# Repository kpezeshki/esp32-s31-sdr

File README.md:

# ESP32-S31 SDR

A low-cost, receive-only, general-purpose SDR. It uses the ESP32-S31's raw I/Q streaming (community "esp-sdr" firmware: continuous 8-bit I/Q at 40 MS/s over gigabit Ethernet) behind a wideband mixer front end.

```
Board B (RF):   SMA ─ ESD ─ SP3T ─┬─ LB: PSA4-5043+ ─ LPF 1.75 GHz ─┐
                                  ├─ MB: PSA4-5043+ ─ BPF 1.75–2.15 ─┤─ SP3T ─ GVA-62+ ─ balun ─ RFFC5072 ─ 2.44 GHz SAW ─ pad ─ U.FL
                                  └─ HB: HPF ─ QPL9503 ─ HPF 3.1 GHz ┘
Board A (base): U.FL ─ ESP32-S31-WROOM-1U (raw I/Q) ─ RGMII ─ YT8531 ─ RJ45 (GbE);  USB-C;  2×10 header → Board B
```

Coverage:

| Band | Range | LO |
|---|---|---|
| LB | 50–1750 MHz | IF+RF |
| MB | 1750–2150 MHz | IF−RF |
| HB | 3.1–6 GHz | RF−IF |
| Native ESP32 (Board A alone) | 2.15–2.8 GHz | none |

The IF is 2440 MHz (61 × 40 MHz).

**Design report** (board renders, copper layers, simulated filters / noise figure / dynamic range, priced BOM, cost per board): [`docs/report/index.html`](docs/report/index.html). It can be served with GitHub Pages from `/docs`.

## Status (2026-11)
- Both boards are placed, routed and DRC-clean to the JLC basic 4-layer process (JLC04161H-3313 stack, 0.45/0.2 mm vias, 0.1/0.1 mm track/space).
- Gerbers, BOM and CPL are in `hw/board_{a,b}/fab/`.
- **Not yet fabricated or measured.** All performance numbers are simulated:

| | LB | MB | HB |
|---|---|---|---|
| Simulated NF | 1.4–2.1 dB | 2.5–3.1 dB | 2.2–3.0 dB |

- Instantaneous dynamic range is ≈44 dB in 40 MHz, limited by the 8-bit ADC.
- Cost: about $87 per system at qty 5, about $68 at qty 10. That is from LCSC prices; the PCB and shipping figures are estimates.
- Before ordering: run a JLC CPL/DFM preview, and check stock for the ESP32-S31 module and the RFFC5072.

## Repository layout
| Path | What |
|---|---|
| `SIGNAL_CHAIN_ANALYSIS.md`, `PART_SELECTION.md`, `RISK_RESEARCH.md`, `COST_PLAN.md` | Analysis: cascade and power levels, frequency plan and spurs, parts, risks, cost |
| `DECISIONS.md` | Decision log (D1–D22) |
| `SPLIT_ARCHITECTURE.md` | Why there are two boards (A: base / B: RF) and the header pinout |
| `analysis/` | Python models: cascade, frequency plan, lumped filter synthesis, cost |
| `em/` | Sonnet EM models of the 0402 filter layouts. EM-in-the-loop optimisation and Monte Carlo (`em/EM_REPORT.md`, `em/filters/FINAL_FILTERS.md`). `RLM_LICENSE` must be set to run Sonnet |
| `hw/design2.py` | Netlists for both boards (`build_a`, `build_b`) |
| `hw/placement_a.py`, `hw/placement_b.py` | Placement and scripted routes. Board A: module escapes, RGMII lanes, USB HS pair. Board B: RF chain exactly as EM-modelled |
| `hw/pcb2.py`, `hw/build_pcb.py`, `hw/footprints.py` | KiCad 10 board generation (pcbnew Python) and custom footprints (`hw/esp32_sdr.pretty`) |
| `hw/fr2.py`, `hw/run_freerouting.sh` | Freerouting flow: DSN export/SES import, incremental passes, scripted fixes. Freerouting runs network-isolated (see `claude_notes/FREEROUTING_AUDIT.md`) |
| `hw/stitch.py`, `hw/rm_dangling.py`, `hw/silk_clean.py`, `hw/render_routed.py` | Post-route: GND stitching, cleanup, silk, renders |
| `hw/board_a/`, `hw/board_b/` | KiCad boards (`*_routed.kicad_pcb`), DRC reports, `fab/` outputs, `shots/` images |
| `hw/report/` | Report generators (`cost_boards.py`, `rf_perf.py`, `build_report.py`) |
| `hw/LAYOUT_STATUS_SPLIT.md` | Layout status and open items |
| `hw/esp32_sdr*.kicad_pcb`, `hw/LAYOUT_STATUS.md`, `hw/router*.py`, `hw/fr_route.py`, `hw/bom.py`, `hw/fab/` | Superseded single-board design, kept for reference (replaced by the two-board split, D15) |

## Reproducing the boards
```
cd hw
python3 fr2.py A export && bash run_freerouting.sh fr-a board_a/esp32sdr_a.dsn board_a/esp32sdr_a.ses board_a/freerouting.log
python3 fr2.py A import && python3 stitch.py board_a/esp32sdr_a_routed.kicad_pcb 3.0 --edge-pitch 3.0 && python3 fr2.py A post
kicad-cli pcb drc --refill-zones --save-board -o board_a/drc_routed.rpt board_a/esp32sdr_a_routed.kicad_pcb
bash fab_export.sh a && python3 bom2.py A          # same for B (stitch pitch 2.5, edge 2.0)
```
Requirements:
- KiCad 10 with its Python bindings;
- Freerouting 2.1 and a Java 21 runtime;
- numpy, scipy and matplotlib;
- Sonnet 19 for the EM models.

Most of the design work was done with Claude (Anthropic) as an engineering agent. `claude_notes/` holds its working notes.

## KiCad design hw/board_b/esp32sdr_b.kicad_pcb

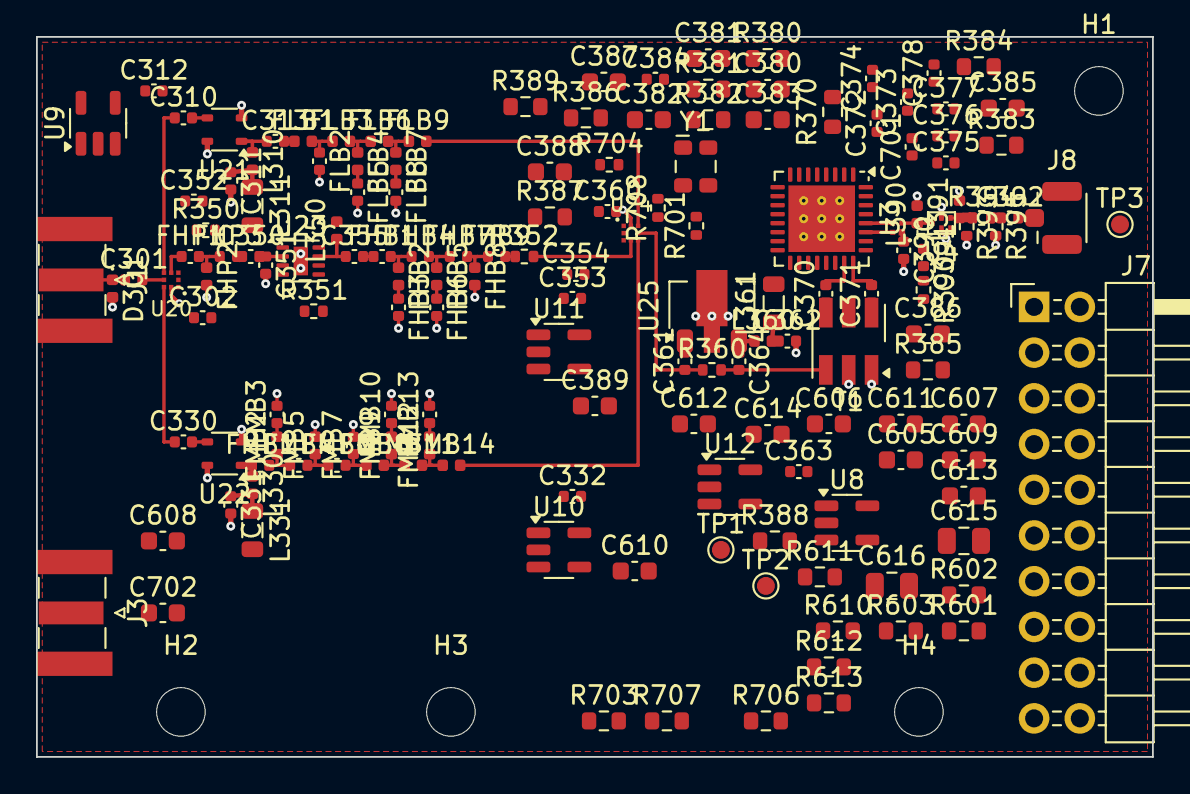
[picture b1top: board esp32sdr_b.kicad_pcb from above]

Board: 4 copper layers, 62.0 x 40.0 mm, 160 parts (0 on the bottom side), 98 nets.

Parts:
C301, C310, C313, C330, C361, C364, C370, C371: 1nF; C_0402_1005Metric
C302, C312, C332, C360, C363, C373, C375, C377, C384, C391, C701: 100nF; C_0402_1005Metric
C311, C331, C352, C353, C362, C390: 100pF; C_0402_1005Metric
C350: 10pF; C_0402_1005Metric
C351: 0.2pF; C_0402_1005Metric
C354: 1uF; C_0402_1005Metric
C355: 5.6pF; C_0402_1005Metric
C372, C374, C376, C378, C392: 33pF; C_0402_1005Metric
C380: 8.2pF; C_0603_1608Metric
C381: 180pF; C_0603_1608Metric
C382, C383: 330pF; C_0603_1608Metric
C385, C386, C387, C388, C389: 33pF; C_0603_1608Metric
C605, C607, C609, C611, C613: 1uF; C_0603_1608Metric
C606, C608, C610, C612, C614: 4.7uF; C_0603_1608Metric
C615: 22uF; C_0805_2012Metric
C616: 10uF; C_0805_2012Metric
C702: 100nF; C_0603_1608Metric
D301: KLXES15AAA1; D_0402_1005Metric
FHB1: 2.4pF; C_0402_1005Metric
FHB2: 2nH; L_0402_1005Metric
FHB3: 3pF; C_0402_1005Metric
FHB4, FHB9: 1pF; C_0402_1005Metric
FHB5: 1.5nH; L_0402_1005Metric
FHB6: 4.7pF; C_0402_1005Metric
FHB7: 0.8pF; C_0402_1005Metric
FHB8: 1.3nH; L_0402_1005Metric
FHP1: 2.4pF; C_0402_1005Metric
FHP2: 2nH; L_0402_1005Metric
FHP3: 1.8pF; C_0402_1005Metric
FLB1, FLB4: 3.9nH; L_0402_1005Metric
FLB2: 2.4pF; C_0402_1005Metric
FLB3: 4.7nH; L_0402_1005Metric
FLB5, FLB8: 1.1pF; C_0402_1005Metric
FLB6: 3.3nH; L_0402_1005Metric
FLB7: 2.7nH; L_0402_1005Metric
FLB9: 1nH; L_0402_1005Metric
FMB1, FMB7: 1.8pF; C_0402_1005Metric
FMB2: 10nH; L_0402_1005Metric
FMB3: 1.1pF; C_0402_1005Metric
FMB4, FMB10: 0.5pF; C_0402_1005Metric
FMB5: 5.1nH; L_0402_1005Metric
FMB6, FMB13: 0.8pF; C_0402_1005Metric
FMB8, FMB11: 3.9nH; L_0402_1005Metric
FMB9: 6.8nH; L_0402_1005Metric
FMB12, FMB14: 3.3nH; L_0402_1005Metric
H1, H2, H3, H4: M2.5; MountingHole_2.7mm_M2.5
J1: SMA_MIX; SMA_Samtec_SMA-J-P-X-ST-EM1_EdgeMount
J3: SMA_REF; SMA_Samtec_SMA-J-P-X-ST-EM1_EdgeMount
J7: To base board; PinHeader_2x10_P2.54mm_Horizontal
J8: U.FL IF out; U.FL_Hirose_U.FL-R-SMT-1_Vertical
L310, L330: 33nH; L_0402_1005Metric
L311, L331, L361: 1uH; L_0805_2012Metric
L350: 18nH; L_0402_1005Metric
L360: 22nH; L_0402_1005Metric
L390, L391: 3.9nH; L_0402_1005Metric
R350: 4.7k; R_0402_1005Metric
R351: 22k; R_0402_1005Metric
R352, R360, R390, R701, R704, R708: 0; R_0402_1005Metric
R370: 51k; R_0603_1608Metric
R380: 22k; R_0603_1608Metric
R381, R382: 470; R_0603_1608Metric
R383, R384, R385, R386, R387, R706: 1k; R_0603_1608Metric
R388, R389: 4.7k; R_0603_1608Metric
R393, R395: 300; R_0402_1005Metric
R394: 18; R_0402_1005Metric
R601, R602, R603, R610, R611, R612, R613: 100k; R_0603_1608Metric
R703: 49.9; R_0603_1608Metric
R707: 390; R_0603_1608Metric
T1: H3-TCM2-63WX+; Mini-Circuits_DB1627
T2: BD2425N50200AHF; Anaren_Xinger_0404_BD2425
TP1: RFFC_LD; TestPoint_Pad_D1.0mm
TP2: 3V0_RF; TestPoint_Pad_D1.0mm
TP3: VGB; TestPoint_Pad_D1.0mm
U3: RFFC5072; QFN-32-1EP_5x5mm_P0.5mm_EP3.7x3.7mm_ThermalVias
U4: SAFEA2G45MC0F0AR00; Filter_1411-5_1.4x1.1mm
U8: TPS7A2030PDBVR; SOT-23-5
U9, U10, U11, U12: TPS7A2045PDBVR; SOT-23-5
U20, U24: BGS13SN8; Infineon_PG-TSNP-8-1_1.1x1.1mm_P0.4mm
U21, U22: PSA4-5043+; SOT-343_SC-70-4
U23: QPL9503; DFN-8-1EP_2x2mm_P0.5mm_EP0.8x1.6mm
U25: GVA-62+; SOT-89-3
Y1: TG2520SMN 40MHz; Oscillator_SMD_SeikoEpson_TG2520SMN-xxx-xxxxxx-4Pin_2.5x2.0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

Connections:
3V0_RF: C372.1, C373.1, C374.1, C375.1, C376.1, C377.1, C606.1, C701.1, R388.2, R390.1, TP2.1, U3.5, U3.19, U3.22, U8.5, Y1.4
3V3: C302.1, C360.1, C616.1, J7.5, U20.1, U24.1
5V0: C605.1, C607.1, C609.1, C611.1, C613.1, C615.1, J7.1, J7.2, U8.1, U8.3, U9.1, U10.1, U11.1, U12.1, U12.3
ESPCLK_DIV: R706.2, R707.1, R708.1
ESP_REFCLK: J7.20, R706.1
EXTREF_AC: C702.2, R703.1, R704.1
EXT_LO_DEC: C378.1, U3.3
EXT_REF: C702.1, J3.1
FHB_M1: FHB2.2, FHB3.1
FHB_M3: FHB5.2, FHB6.1
FHB_N1: FHB1.2, FHB2.1, FHB4.1
FHB_N2: FHB4.2, FHB5.1, FHB7.1
FHB_N3: FHB7.2, FHB8.1, FHB9.1
FHP_N1: FHP1.2, FHP2.1, FHP3.1
FLB_M3: FLB4.2, FLB5.1
FLB_M5: FLB7.2, FLB8.1
FLB_N1: FLB1.2, FLB2.1, FLB3.1
FLB_N2: FLB3.2, FLB4.1, FLB6.1
FLB_N3: FLB6.2, FLB7.1, FLB9.1
FMB_M1: FMB2.2, FMB3.1
FMB_M7: FMB9.2, FMB10.1
FMB_M9: FMB12.2, FMB13.1
FMB_N1: FMB1.2, FMB2.1, FMB4.1
FMB_N2: FMB4.2, FMB5.1, FMB6.1
FMB_N3: FMB6.2, FMB7.1, FMB8.1
FMB_N4: FMB8.2, FMB9.1, FMB11.1
FMB_N5: FMB11.2, FMB12.1, FMB14.1
GB_CHK: C362.1, L360.2, L361.1
GB_I: C361.2, U25.1
GB_O: C364.1, L360.1, U25.3
GND: C302.2, C311.2, C312.2, C331.2, C332.2, C351.2, C352.2, C353.2, C354.2, C360.2, C362.2, C363.2, C372.2, C373.2, C374.2, C375.2, C376.2, C377.2, C378.2, C382.2, C383.2, C385.2, C386.2, C387.2, C388.2, C389.2, C390.2, C391.2, C605.2, C606.2, C607.2, C608.2, C609.2, C610.2, C611.2, C612.2, C613.2, C614.2, C615.2, C616.2, C701.2, D301.2, FHB3.2, FHB6.2, FHB8.2, FHP2.2, FLB2.2, FLB5.2, FLB8.2, FMB3.2, FMB5.2, FMB7.2, FMB10.2, FMB13.2, J1.2, J3.2, J7.3, J7.4, J7.6, J8.2, L390.2, L391.2, R351.2, R370.2, R389.2, R393.2, R395.2, R601.2, R602.2, R603.2, R610.2, R611.2, R612.2, R613.2, R703.2, R707.2, T1.1, T1.2, U3.12, U3.33, U4.2, U4.3, U4.5, U8.2, U9.2, U10.2, U11.2, U12.2, U20.8, U21.2, U21.4, U22.2, U22.4, U23.4, U23.6, U23.9, U24.8, U25.2, Y1.2
HB_F_IN: C355.2, FHB1.1
HB_HPF_O: FHB9.2, R352.1
HB_IN: FHP1.1, U20.4
HB_LNA_I: C350.2, C351.1, U23.2
HB_LNA_O: C355.1, L350.1, U23.7
HB_OUT: R352.2, U24.4
HB_PRE_O: C350.1, FHP3.2
HB_SD: R351.1, U23.5
HB_VBIAS: C352.1, R350.2, U23.1
IF_CT: C390.1, C391.1, R390.2, T2.1
IF_OP_N: T2.4, U3.27
IF_OP_P: T2.3, U3.28
IF_OUT: C392.2, J8.1
IF_SAW_O: L391.1, R393.1, R394.1, U4.4
IF_SE: L390.1, T2.2, U4.1
LB_CHK: C311.1, L310.2, L311.1
LB_F_IN: C313.2, FLB1.1
LB_IN: C310.1, U20.5
LB_LNA_I: C310.2, U21.3
LB_LNA_O: C313.1, L310.1, U21.1
LB_OUT: FLB9.2, U24.7
LDO_EN_HB: J7.19, R603.1, U11.3
LDO_EN_LB: J7.17, R601.1, U9.3
LDO_EN_MB: J7.18, R602.1, U10.3
LF1: C380.1, R380.1, U3.6
LF2: C380.2, C381.2, R381.1, U3.7
LF3: C383.1, R382.2, U3.8
LF_A: C381.1, R380.2
LF_B: C382.1, R381.2, R382.1
MB_CHK: C331.1, L330.2, L331.1
MB_IN: C330.1, U20.7
MB_LNA_I: C330.2, U22.3
MB_LNA_O: FMB1.1, L330.1, U22.1
MB_OUT: FMB14.2, U24.5
MIX_DRV: C364.2, R360.2, T1.3
MIX_IN_N: C371.1, T1.6
MIX_IN_P: C370.1, T1.4
MIX_IPN: C371.2, U3.24
MIX_IPP: C370.2, U3.23
PAD_O: C392.1, R394.2, R395.1
REFCLK_RF: C384.1, R701.2, R704.2, R708.2
REF_IN: C384.2, U3.10
RFFC_ENBL: J7.10, R386.1
RFFC_ENBL_I: C388.1, R386.2, U3.1
RFFC_ENX: J7.9, R385.1
RFFC_ENX_I: C387.1, R385.2, U3.30
RFFC_LD: J7.12, TP1.1, U3.26
RFFC_MODE: R389.1, U3.9
RFFC_RESETX: J7.11, R387.1
RFFC_RESETX_I: C389.1, R387.2, R388.1, U3.29
RFFC_REXT: R370.1, U3.4
RFFC_SCLK: J7.7, R383.1
RFFC_SCLK_I: C385.1, R383.2, U3.31
RFFC_SDATA: J7.8, R384.1
RFFC_SDATA_I: C386.1, R384.2, U3.32
RF_IN_SMA: C301.1, D301.1, J1.1
SW1_COM: C301.2, U20.6
SW2_COM: C361.1, R360.1, U24.6
SW2_V1: J7.15, R612.1, U24.3
SW2_V2: J7.16, R613.1, U24.2
SW_V1: J7.13, R610.1, U20.3
SW_V2: J7.14, R611.1, U20.2
TCXO_OUT: R701.1, Y1.3
VGB: C363.1, C614.1, L361.2, TP3.1, U12.5
VLNA_HB: C353.1, C354.1, C612.1, L350.2, R350.1, U11.5
VLNA_LB: C312.1, C608.1, L311.2, U9.5
VLNA_MB: C332.1, C610.1, L331.2, U10.5

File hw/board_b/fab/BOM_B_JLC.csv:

Comment,Designator,Footprint,LCSC Part #
TG2520SMN 40MHz,Y1,Oscillator_SMD_SeikoEpson_TG2520SMN-xxx-xxxxxx-4Pin_2.5x2.0mm,C3007519
100nF,"C302,C312,C332,C360,C363,C373,C375,C377,C384,C391,C701",C_0402_1005Metric,C1525
0,"R352,R390,R701",R_0402_1005Metric,C17168
KLXES15AAA1,D301,D_0402_1005Metric,C2892490
1nF,"C301,C310,C313,C330,C361,C364,C370,C371",C_0402_1005Metric,C1523
BGS13SN8,"U20,U24",Infineon_PG-TSNP-8-1_1.1x1.1mm_P0.4mm,C3312946
PSA4-5043+,"U21,U22",SOT-343_SC-70-4,C5240848
33nH,"L310,L330",L_0402_1005Metric,C113114
100pF,"C311,C331,C352,C353,C362,C390",C_0402_1005Metric,C1546
3.9nH,"FLB1,FLB4,FMB11,FMB8,L390,L391",L_0402_1005Metric,C98062
2.4pF,"FHB1,FHP1,FLB2",C_0402_1005Metric,C88889
4.7nH,FLB3,L_0402_1005Metric,C98064
1.1pF,"FLB5,FLB8,FMB3",C_0402_1005Metric,C88879
3.3nH,"FLB6,FMB12,FMB14",L_0402_1005Metric,C98061
2.7nH,FLB7,L_0402_1005Metric,C91239
1nH,FLB9,L_0402_1005Metric,C162538
1.8pF,"FHP3,FMB1,FMB7",C_0402_1005Metric,C76903
10nH,FMB2,L_0402_1005Metric,C90642
0.5pF,"FMB10,FMB4",C_0402_1005Metric,C76912
5.1nH,FMB5,L_0402_1005Metric,C113117
0.8pF,"FHB7,FMB13,FMB6",C_0402_1005Metric,C88902
6.8nH,FMB9,L_0402_1005Metric,C82919
2nH,"FHB2,FHP2",L_0402_1005Metric,C2986275
10pF,C350,C_0402_1005Metric,C85873
QPL9503,U23,DFN-8-1EP_2x2mm_P0.5mm_EP0.8x1.6mm,C470924
4.7k,R350,R_0402_1005Metric,C25900
18nH,L350,L_0402_1005Metric,C91622
1uF,C354,C_0402_1005Metric,C52923
22k,R351,R_0402_1005Metric,C25768
5.6pF,C355,C_0402_1005Metric,C161329
3pF,FHB3,C_0402_1005Metric,C88891
1pF,"FHB4,FHB9",C_0402_1005Metric,C72134
1.5nH,FHB5,L_0402_1005Metric,C18221
4.7pF,FHB6,C_0402_1005Metric,C161327
1.3nH,FHB8,L_0402_1005Metric,C91238
GVA-62+,U25,SOT-89-3,C5445184
22nH,L360,L_0402_1005Metric,C86129
H3-TCM2-63WX+,T1,Mini-Circuits_DB1627,C22383437
RFFC5072,U3,QFN-32-1EP_5x5mm_P0.5mm_EP3.7x3.7mm_ThermalVias,C3034742
33pF,"C372,C374,C376,C378,C392",C_0402_1005Metric,C426031
BD2425N50200AHF,T2,Anaren_Xinger_0404_BD2425,C502748
SAFEA2G45MC0F0AR00,U4,Filter_1411-5_1.4x1.1mm,C910550
300,"R393,R395",R_0402_1005Metric,C25102
18,R394,R_0402_1005Metric,C25113
U.FL IF out,J8,U.FL_Hirose_U.FL-R-SMT-1_Vertical,C5137195

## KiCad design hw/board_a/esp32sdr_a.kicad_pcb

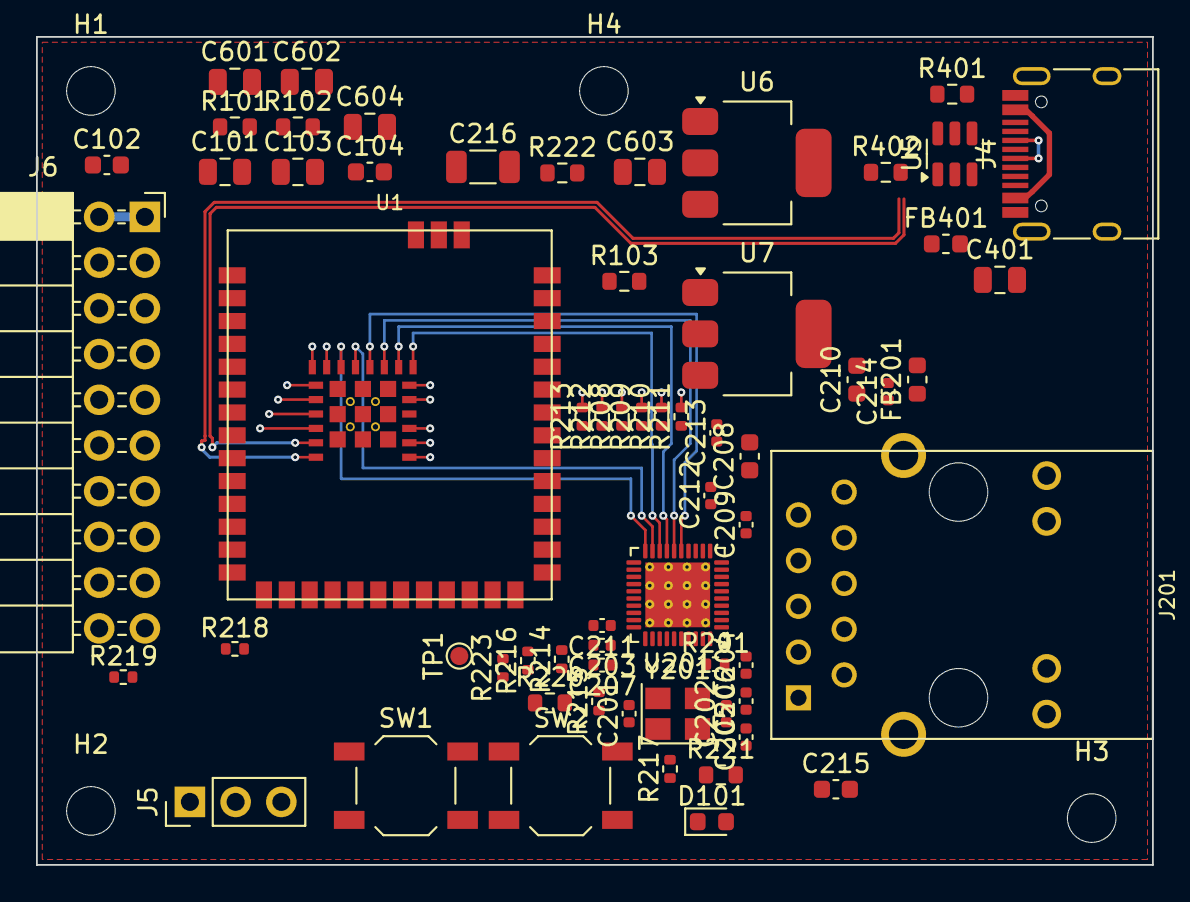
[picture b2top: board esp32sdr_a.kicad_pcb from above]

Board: 4 copper layers, 62.0 x 46.0 mm, 67 parts (0 on the bottom side), 72 nets.

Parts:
C101, C401, C601, C603: 22uF; C_0805_2012Metric
C102: 100nF; C_0603_1608Metric
C103, C602, C604: 10uF; C_0805_2012Metric
C104: 1uF; C_0603_1608Metric
C201, C202: 15 pF 50V C0G; C_0402_1005Metric
C203, C204, C205, C206, C207, C209, C211, C212, C213, C214: 100 nF 16V; C_0402_1005Metric
C208, C210: 10 uF 10V; C_0603_1608Metric
C215: 100 nF 50V; C_0603_1608Metric
C216: 1 nF 2 kV; C_1206_3216Metric
D101: LED; LED_0603_1608Metric
FB201: 120 ohm @100 MHz, 2 A; L_0603_1608Metric
FB401: 120R@100MHz; L_0603_1608Metric
H1, H2, H3, H4: M2.5; MountingHole_2.7mm_M2.5
J4: USB-C; USB_C_Receptacle_HRO_TYPE-C-31-M-12
J5: UART; PinHeader_1x03_P2.54mm_Vertical
J6: To RF board; PinSocket_2x10_P2.54mm_Horizontal
J201: RJ45 1000BASE-T magjack, integrated magnetics + B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; RJ45_HanRun_HR911130C
R101, R102: 10k; R_0603_1608Metric
R103: 1k; R_0603_1608Metric
R201: 2.49k 1%; R_0402_1005Metric
R208, R209, R210, R211, R212, R213: 33R 1%; R_0402_1005Metric
R214, R215, R216, R217, R218, R219: 4.7k 1%; R_0402_1005Metric
R220, R221: 330R 1%; R_0603_1608Metric
R222: 0R; R_0603_1608Metric
R223: 0R; R_0402_1005Metric
R401, R402: 5.1k; R_0603_1608Metric
SW1: RESET; SW_SPST_TL3342
SW2: BOOT; SW_SPST_TL3342
TP1: GPIO60; TestPoint_Pad_D1.0mm
U1: ESP32-S31-WROOM-1U-N16R16V; Espressif_ESP32-S31-WROOM-1U
U5: USBLC6-2SC6; SOT-23-6
U6, U7: AMS1117-3.3; SOT-223-3_TabPin2
U201: YT8531DC-CA; QFN-40-1EP_5x5mm_P0.4mm_EP3.6x3.6mm_ThermalVias
Y201: 25 MHz, CL 12 pF, +/-10 ppm; Crystal_SMD_3225-4Pin_3.2x2.5mm

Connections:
3V3: C101.1, C102.1, C103.1, C601.1, J6.5, R101.1, R102.1, U1.2, U6.2
3V3_PHY: C603.1, FB201.1, U7.2
5V0: C401.1, C602.1, C604.1, FB401.2, J6.1, J6.2, U6.3, U7.3
BOOT: R102.2, SW2.1, SW2.2, U1.27
CC1: J4.A5, R401.1
CC2: J4.B5, R402.1
CHIP_PU: C104.1, R101.2, SW1.1, SW1.2, U1.3
ESP_REFCLK: J6.20, U1.35
ETH_INTN: R217.1, R223.1, U201.31
ETH_MDC: U1.7, U201.13
ETH_MDIO: R218.1, U1.10, U201.14
ETH_PHY_RST_N: R219.1, U1.11, U201.12
ETH_RXD0: R208.2, U1.53
ETH_RXD1: R209.2, U1.52
ETH_RXD2: R210.2, U1.51
ETH_RXD3: R211.2, U1.50
ETH_RX_CLK: R213.2, U1.48
ETH_RX_CTL: R212.2, U1.49
ETH_TXD0: U1.42, U201.18
ETH_TXD1: U1.43, U201.17
ETH_TXD2: U1.44, U201.16
ETH_TXD3: U1.45, U201.15
ETH_TX_CLK: U1.47, U201.20
ETH_TX_CTL: U1.46, U201.19
GND: C101.2, C102.2, C103.2, C104.2, C201.2, C202.2, C203.2, C204.2, C205.2, C206.2, C207.2, C208.2, C209.2, C210.2, C211.2, C212.2, C213.2, C214.2, C215.2, C216.2, C401.2, C601.2, C602.2, C603.2, C604.2, D101.1, J4.A1, J4.A12, J4.B1, J4.B12, J4.S1, J5.1, J6.3, J6.4, J6.6, J201.12, J201.13, R201.2, R214.2, R215.2, R222.2, R401.2, R402.2, U1.1, U1.40, U1.41, U1.62, U1.64, U5.2, U6.1, U7.1, U201.41, Y201.2, Y201.4
GND_CHASSIS: C216.1, J201.10, R222.1
GPIO60: TP1.1, U1.26
LDO_EN_HB: J6.19, U1.38
LDO_EN_LB: J6.17, U1.6
LDO_EN_MB: J6.18, U1.34
LED_A: D101.2, R103.2
LED_GRN_A: J201.11, R220.2
LED_STAT: R103.1, U1.39
LED_YEL_A: J201.14, R221.2
MAG_CT: C215.1, J201.1
MDI0_N: J201.3, U201.2
MDI0_P: J201.2, U201.1
MDI1_N: J201.7, U201.5
MDI1_P: J201.4, U201.4
MDI2_N: J201.6, U201.7
MDI2_P: J201.5, U201.6
MDI3_N: J201.9, U201.10
MDI3_P: J201.8, U201.9
PHY_3V3: C208.1, C209.1, C210.1, C211.1, C212.1, C213.1, C214.1, FB201.2, R216.2, R217.2, R218.2, R219.2, U201.11, U201.28, U201.29, U201.40
PHY_CFG_EXT: R216.1, U201.32
PHY_LED1: R215.1, R221.1, U201.33
PHY_LED2: R214.1, R220.1, U201.34
PHY_RBIAS: R201.1, U201.39
PHY_RXD0: R208.1, U201.25
PHY_RXD1: R209.1, U201.24
PHY_RXD2: R210.1, U201.23
PHY_RXD3: R211.1, U201.22
PHY_RX_CLK: R213.1, U201.27
PHY_RX_CTL: R212.1, U201.26
PHY_VDDL: C203.1, C204.1, C205.1, C206.1, C207.1, U201.3, U201.8, U201.21, U201.30, U201.38
PHY_XI: C201.1, U201.36, Y201.1
PHY_XO: C202.1, U201.37, Y201.3
RFFC_ENBL: J6.10, U1.56
RFFC_ENX: J6.9, U1.33
RFFC_LD: J6.12, U1.58
RFFC_RESETX: J6.11, U1.57
RFFC_SCLK: J6.7, U1.31
RFFC_SDATA: J6.8, U1.32
SW2_V1: J6.15, U1.60
SW2_V2: J6.16, U1.61
SW_V1: J6.13, U1.4
SW_V2: J6.14, U1.5
U0RXD: J5.3, U1.36
U0TXD: J5.2, U1.37
USB_DM: J4.A7, J4.B7, U1.54, U5.3, U5.4
USB_DP: J4.A6, J4.B6, U1.55, U5.1, U5.6
VBUS: FB401.1, J4.A4, J4.A9, J4.B4, J4.B9, U5.5

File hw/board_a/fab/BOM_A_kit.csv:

LCSC Part #,Qty per board,Designators,Value,Footprint,Note
,1,U1,ESP32-S31-WROOM-1U-N16R16V,Espressif_ESP32-S31-WROOM-1U,reflow in house (A1); stock 0 at LCSC 2026-11-10; U.FL ANT1 -> patch cable to Bo
C45783,4,"C101,C401,C601,C603",22uF,C_0805_2012Metric,
C14663,1,C102,100nF,C_0603_1608Metric,
C15850,3,"C103,C602,C604",10uF,C_0805_2012Metric,
C25804,2,"R101,R102",10k,R_0603_1608Metric,
C15849,1,C104,1uF,C_0603_1608Metric,EN RC delay
C318884,1,SW1,RESET,SW_SPST_TL3342,
C318884,1,SW2,BOOT,SW_SPST_TL3342,
C49257,1,J5,UART,PinHeader_1x03_P2.54mm_Vertical,
C21190,1,R103,1k,R_0603_1608Metric,
C72043,1,D101,LED,LED_0603_1608Metric,
,1,TP1,GPIO60,TestPoint_Pad_D1.0mm,
C165948,1,J4,USB-C,USB_C_Receptacle_HRO_TYPE-C-31-M-12,
C23186,2,"R401,R402",5.1k,R_0603_1608Metric,
C7519,1,U5,USBLC6-2SC6,SOT-23-6,
C1015,1,FB401,120R@100MHz,L_0603_1608Metric,
C6186,2,"U6,U7",AMS1117-3.3,SOT-223-3_TabPin2,3V3: module (+ Board B switches)
C239361,1,J6,To RF board,PinSocket_2x10_P2.54mm_Horizontal,2x10 2.54 mm right-angle female; doubles as GPIO header when used alone
C47544379,1,U201,YT8531DC-CA,QFN-40-1EP_5x5mm_P0.4mm_EP3.6x3.6mm_ThermalVias,"JLC record is named '【邮寄专用】' ('for mailing only') and has no LCSC page link, unl"
C9006,1,Y201,"25 MHz, CL 12 pF, +/-10 ppm",Crystal_SMD_3225-4Pin_3.2x2.5mm,"YT8531 requires +/-50 ppm, ESR <= 50 ohm, drive <= 0.5 mW. ESR of C9006 is not c"
C1548,2,"C201,C202",15 pF 50V C0G,C_0402_1005Metric,Load cap for CL = 12 pF: 15/2 + ~4 pF stray = ~11.5 pF. CoreBoard uses 8.2 pF (C
C25884,1,R201,2.49k 1%,R_0402_1005Metric,Datasheet: 2.49k +/-1% required
C1525,10,"C203,C204,C205,C206,C207,C209,C211,C212,C213,C214",100 nF 16V,C_0402_1005Metric,
C19702,2,"C208,C210",10 uF 10V,C_0603_1608Metric,The CoreBoard uses 4.7 uF here. We use 10 uF so the board shares one bulk value.
C14709,1,FB201,"120 ohm @100 MHz, 2 A",L_0603_1608Metric,"The CoreBoard uses BLM18PG330SN1D (33 ohm, 3 A; C88984, extended). Either works."
C25105,6,"R208,R209,R210,R211,R212,R213",33R 1%,R_0402_1005Metric,RX line (PHY drives). Pin 1 is the PHY side. Place at the PHY (source terminatio
C25900,6,"R214,R215,R216,R217,R218,R219",4.7k 1%,R_0402_1005Metric,CFG_LDO1 = 0
C23138,2,"R220,R221",330R 1%,R_0603_1608Metric,"LED2 = 1000M link/activity, drives green LED (J201 pin 11). Active high, as on t"
C14663,1,C215,100 nF 50V,C_0603_1608Metric,"Chip-side centre-tap decoupling. The HR911130C ties all 4 CTs to P1, so one cap "
C50933,1,J201,"RJ45 1000BASE-T magjack, integrated magnetics + Bob Smith, G/Y LEDs",RJ45_HanRun_HR911130C,Replaces CoreBoard T1 (ML-G24P02S) + J8 (MRD(W)A101A2) + R75/76/78/80 (75R) + C7
C21189,1,R222,0R,R_0603_1608Metric,Joins chassis to logic GND at a single point near the jack. Fit 0R (as on the Co

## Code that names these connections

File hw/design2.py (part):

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    g = "module"
    m = {i: "NC" for i in range(1, 65)}
    m.update({1: "GND", 2: "3V3", 3: "CHIP_PU", 4: "SW_V1", 5: "SW_V2", 6: "LDO_EN_LB", 7: "ETH_MDC", 10: "ETH_MDIO",
              11: "ETH_PHY_RST_N", 26: "GPIO60", 27: "BOOT", 31: "RFFC_SCLK", 32: "RFFC_SDATA", 33: "RFFC_ENX",
              34: "LDO_EN_MB", 35: "ESP_REFCLK", 36: "U0RXD", 37: "U0TXD", 38: "LDO_EN_HB", 39: "LED_STAT", 40: "GND", 41: "GND",
              42: "ETH_TXD0", 43: "ETH_TXD1", 44: "ETH_TXD2", 45: "ETH_TXD3", 46: "ETH_TX_CTL", 47: "ETH_TX_CLK",
              48: "ETH_RX_CLK", 49: "ETH_RX_CTL", 50: "ETH_RXD3", 51: "ETH_RXD2", 52: "ETH_RXD1", 53: "ETH_RXD0",
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    D.add("J5", "UART", "HDR1x3", {1: "GND", 2: "U0TXD", 3: "U0RXD"}, "C49257", "hand", group=g)
    R("R103", "1k", "LED_STAT", "LED_A", group=g)
    D.add("D101", "LED", "LED0603", {1: "GND", 2: "LED_A"}, lc("LED0603", "G"), "hand", group=g)
    D.add("TP1", "GPIO60", "TestPoint:TestPoint_Pad_D1.0mm", {1: "GPIO60"}, "", "hand", group=g)
    # USB-C: power in + HS USB data
    g = "usb"
    D.add("J4", "USB-C", "USBC", {"A1": "GND", "B12": "GND", "A12": "GND", "B1": "GND", "A4": "VBUS", "B9": "VBUS", "A9": "VBUS", "B4": "VBUS",
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
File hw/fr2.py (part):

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# ("track", net, layer, [(x, y), ...], width) or ("via", net, (x, y)).  Locked, so the router keeps them.
FIXUPS = {
    "B": [
        # RFFC5072 VDD pins 19 / 22 (bottom row, 0.5 mm pitch; 20/21 NC; the locked MIX_IPP pre-route runs at y 13.55
        # under pin 22): join both pins with a stub at y 13.2 (0.15 mm from the NC pad ends and from MIX_IPP), then one
        # via at (42.6, 14.2) (~1 mm from all other copper).  The router links the via to the 3V0_RF network.
        ("track", "3V0_RF", pcbnew.F_Cu, [(44.35, 12.55), (44.35, 13.2), (42.85, 13.2)], 0.2),
        ("track", "3V0_RF", pcbnew.F_Cu, [(42.85, 12.55), (42.85, 13.2), (42.6, 13.45), (42.6, 14.2)], 0.2),
        ("via", "3V0_RF", (42.6, 14.2)),
        # U12 (TPS7A20, SOT-23-5) GND pin 2 sits between the two 5V0 pins: escape under the body to a via at x 38.6
        # (0.42 mm from pins 4/5).  LF_B and RFFC_RESETX_I had been routed under the LDO body and are ripped.
        ("track", "GND", pcbnew.F_Cu, [(37.36, 25.0), (38.6, 25.0)], 0.3),
        ("via", "GND", (38.6, 25.0)),
        # rip the router's wires that block the vias (VGB B.Cu trunk, LF_B / RESETX under U12) or overlapped each
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    ],
    "B": [
        # J7 (header to Board A) pins 1 and 2 are both 5V0 (2.54 mm apart): strap them so both pins carry supply current
        ("track", "5V0", pcbnew.B_Cu, [(55.40, 15.0), (57.94, 15.0)], 0.5),   # B.Cu: RFFC_SDATA passes between the pins on F.Cu
    ],
}

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
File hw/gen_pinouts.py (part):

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    "7":  {"name": "LFILT2", "function": "Loop-filter op-amp output (noise-sensitive)"},
    "8":  {"name": "LFILT3", "function": "VCO tuning input (noise-sensitive)"},
    "9":  {"name": "MODE/GPO6", "function": "Mode select (path 1/2 register bank in pin mode). GPO6 if SPI-controlled."},
    "10": {"name": "REF_IN", "function": "Reference input 10-104 MHz, 0.5-1.5 Vpp, AC-coupled (labelled XTALP on eval sheet)"},
    "11": {"name": "NC", "function": "No connect (labelled XTALN on eval sheet, unconnected)"},
    "12": {"name": "TM", "function": "Test mode - connect to GND"},
    "13": {"name": "NC", "function": "MIX1_IPN on RFFC5071; NC on RFFC5072"},
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# ---------------------------------------------------------------- 16. UART header + tact switches
P["UART_HEADER_1x3"] = {"mfr": "BOOMELE (any)", "mpn": "2.54-1*3P pin header", "lcsc": "C49257",
  "function": "3-pin UART0 header (hand-soldered, D11)",
  "source": "JLC parts API 2026-11-09 (C49257, extended); ESP32-S31 HW design guidelines 1.3.7 (U0TXD=GPIO58, U0RXD=GPIO59, 499R series on TX)",
  "package": {"name": "1x3 2.54 mm THT"}, "kicad_footprint": "Connector_PinHeader_2.54mm:PinHeader_1x03_P2.54mm_Vertical",
  "kicad_footprint_check": "exists",
  "pins": {"1": {"name": "GND", "function": "Ground"}, "2": {"name": "TXD (from ESP32)", "function": "ESP32 U0TXD = GPIO58 via 499R"},
           "3": {"name": "RXD (into ESP32)", "function": "ESP32 U0RXD = GPIO59"}},
  "app_circuit": [{"ref_hint": "R_TX", "value": "499R", "package": "0603", "connects": ["ESP32 GPIO58", "J.2"], "source": "S31 HW guide 1.3.7"}],
  "notes": ["Order/labels are a suggestion; silkscreen them."]}
P["TACT_SW_TS-1187A-B-A-B"] = {"mfr": "XKB Connection", "mpn": "TS-1187A-B-A-B", "lcsc": "C318884",
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  "kicad_footprint_check": "TL3342 pads 1.7x1.0 at (+-3.15, +-1.9) cover the XKB land (1.0x0.75 at +-3.0, +-1.875). TL3342 pad '1' = top pair, '2' = bottom pair; XKB: A-B (top pair) internally connected, C-D (bottom pair) connected, switch between pairs -> matches.",
  "pins": {"1 (A,B)": {"name": "Contact 1", "function": "pair, internally shorted"}, "2 (C,D)": {"name": "Contact 2", "function": "pair, internally shorted"}},
  "app_circuit": [
    {"ref_hint": "SW_BOOT", "value": "TS-1187A-B-A-B", "package": "SMD", "connects": ["ESP32 GPIO61", "GND"], "source": "S31 HW guide Table 4: GPIO61=0 at reset release -> Joint Download Boot (GPIO60 must be 1)"},
    {"ref_hint": "R_BOOT", "value": "10k pull-up (optional; check internal pull in S31 datasheet)", "package": "0402", "connects": ["GPIO61", "3V3"], "source": "UNVERIFIED default pull"},
    {"ref_hint": "SW_RST", "value": "TS-1187A-B-A-B", "package": "SMD", "connects": ["ESP32 CHIP_PU", "GND"], "source": "S31 HW guide 1.3.x CHIP_PU"},
    {"ref_hint": "R_PU", "value": "10k", "package": "0402", "connects": ["CHIP_PU", "3V3"], "source": "S31 HW guide: RC delay R=10k"},
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
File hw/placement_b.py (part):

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    B.place("L331", o[0] + 0.6, y_mbf + 3.6, -90); B.track(pp(B, "L330", "2"), pp(B, "L331", "1"), 0.25, net="MB_CHK")
    B.place("C331", o[0] - 0.6, y_mbf + 2.2, -90); B.track(pp(B, "C331", "1"), pp(B, "L330", "2"), 0.25, net="MB_CHK"); gnd_via_at(B, "C331", "2")
    xe_mb = BP.place_ladder(B, "FMB", "MB_BPF2", o[0] + 0.0, y_mbf, "MB_LNA_O", "MB_OUT", flip=True)
    # ---- SP3T_out (rot 0): RFin MR, RF2 TR <- LB, RF3 BM <- HB, RF1 BR <- MB  (LB_OUT=RF1 net, so ports are re-labelled in design)
    B.place("U24", XS_OUT, YS_OUT, 0)
    B.place("C360", XS_OUT - 1.3, YS_OUT - 1.2, 0)
    # branch outputs into SP3T_out
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    "Y1": (36.6, 7.2, 0), "U8": (45.0, 27.0, 0), "U9": (3.4, 4.8, 90), "U10": (29.0, 28.5, 0), "U11": (29.0, 17.5, 0),
    "U12": (38.5, 25.0, 0), "J3": (2.1, 32.0, -90), "H1": (59.0, 3.0, 0), "H2": (8.0, 37.5, 0), "H3": (23.0, 37.5, 0), "H4": (49.0, 37.5, 0),
    # RFFC5072 loop filter (LF1 = pin 6, LF2 = pin 7, LF3/VTUNE = pin 8 on U3's north row at x 42.85/42.35/41.85,
    # y 7.65): compact 3x3 cluster just NW of those pins (auto-placement had scattered it, LF_B ran 61 mm with 3 vias).
    # Column nearest the pins first: C383 (LF3), C380 (LF1-LF2), R380 (LF1-LF_A).  Rows clear Y1 (y >= 5.5).
    "C383": (40.6, 4.6, 0), "R382": (37.3, 4.6, 0), "C382": (34.0, 4.6, 0),
    "C380": (40.6, 2.9, 0), "R381": (37.3, 2.9, 0),
    "R380": (40.6, 1.2, 0), "C381": (37.3, 1.2, 0),
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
